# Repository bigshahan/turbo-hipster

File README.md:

turbo-hipster
=============

# Running the site for devlopment (Windows) (Works for Linux/OS X too)

Install git, VirtualBox, Vagrant. Then from git project folder:

	vagrant up
	vagrant ssh
	cd /vagrant
	jekyll serve -w

# Running the site for development (Linux and OS X)

Make sure ruby and nodejs is installed. Then from the git project folder, do:
	gem install rmagick
	gem install jekyll
	bundle install

then:

	jekyll serve -w

# Adding a New Project

# Setting Up the Production Server

# Helpful Commands

To check status in github powershell:

	git status -s

To update:

	git pull

To make changes:

	git status -s
	git add filename				// Variations for making changes
	git commit -m "comment here"	//
	git push

Shortcut for updating old files:

	Replace above variation // with
	git commit -a -m "comment here"

Shortcut for adding all files in a folder:

	Replace above variation // with
	git add foldername/*
	git commit -m "comment here"
	
	example:
	git add images/pipettebot/*
	git commit -m "Adds all files in local repository in images/pipettebot/ to main branch online"

# Enabling a Sidebar for a page

	Page Name
	=========

	<div class="col-sm-4">
		<ul class="nav nav-pills nav-stacked">
			{% sidebar "content1", "Content 1" %}

			{% sidebar "content2", "Content 2" %}

			{% sidebar "content3", "Content 3" %}
		</ul>
	</div>

	<div id="content1" class="sidebar-content col-sm-8">
		<h1>Content 1</h1>
		<p>text</p>
	</div>

	<div id="content2" class="sidebar-content col-sm-8">
		<h1>Content 2</h1>
		<p>text2</p>
	</div>

	<div id="content3" class="sidebar-content col-sm-8">
		<h1>Content 3</h1>
		<p>text3</p>
	</div>

# Pushing to the FTP server
(only works on Mac/Linux & must have lftp installed. The vagrant image has this installed) 

cd into the project folder
./upload.sh 

Username & FTP server is set in the deploy.x file

# Using Git GUI
Use the folder where the repository is held from github

	Click rescan button to check if any new changes have been made
	Click files you want to change in the unstaged changes section and press stage changed button
	Then after selecting all desired files press commit button
	Then press push button to make changes to the main repository

# References
- Boostrap: http://getbootstrap.com/
- Vagrant / Jekyll: https://coderwall.com/p/xrfadg
- Jekyll documentation: http://jekyllrb.com/
- Markdown Syntax: https://github.com/adam-p/markdown-here/wiki/Markdown-Cheatsheet

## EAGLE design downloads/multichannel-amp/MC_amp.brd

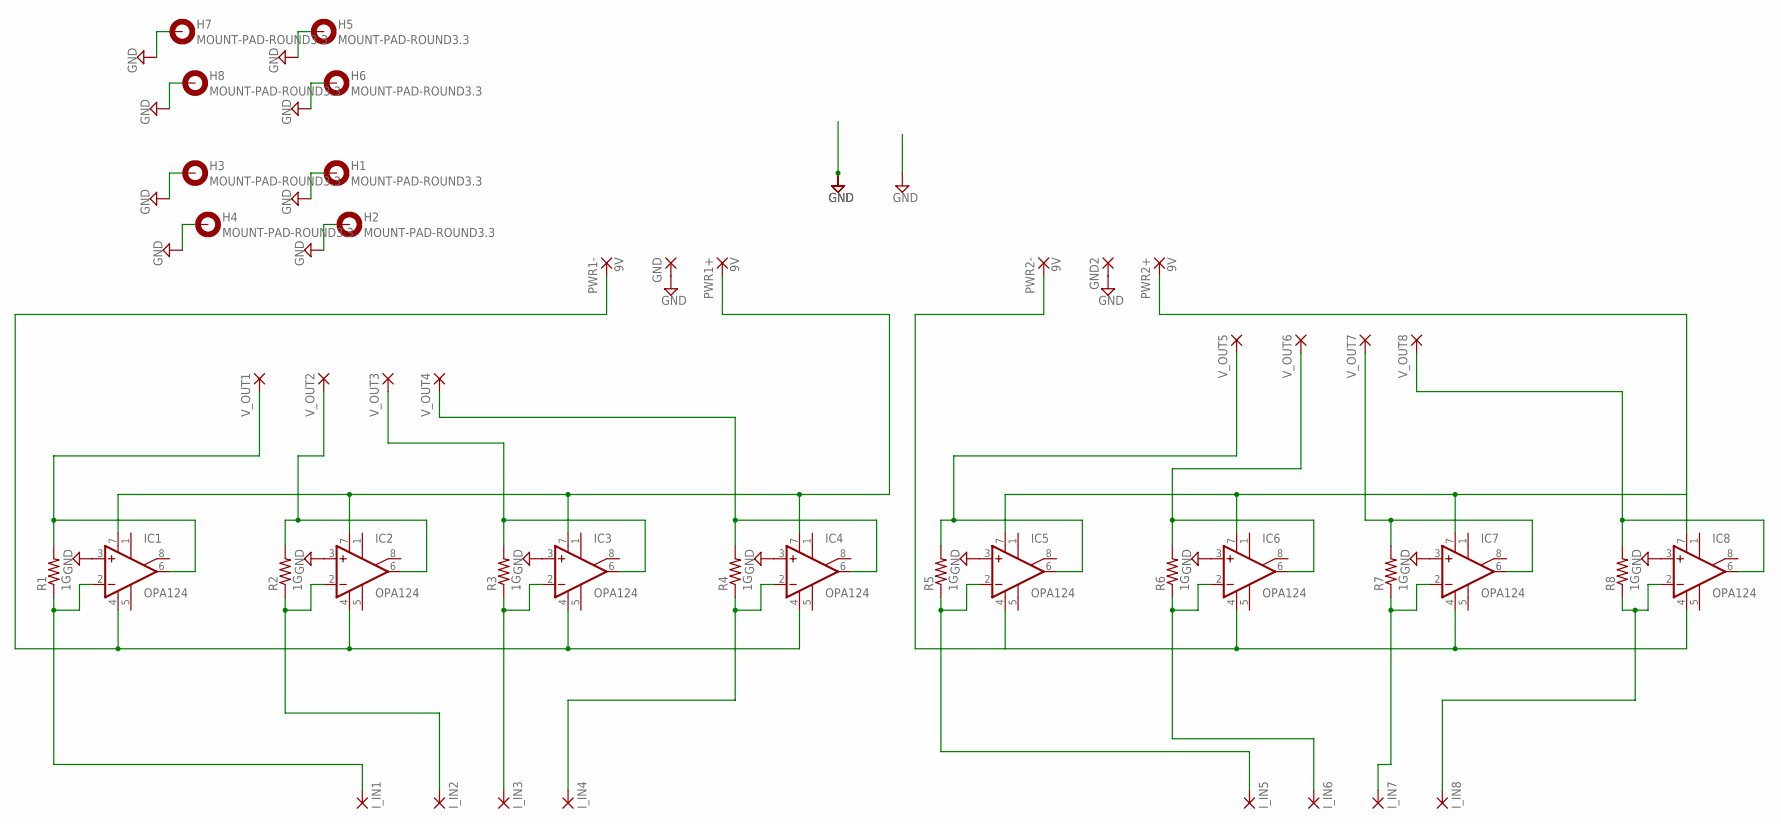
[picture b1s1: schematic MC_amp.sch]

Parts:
GND, GND2: 1,6/0,8
H1, H2, H3, H4, H5, H6, H7, H8: MOUNT-PAD-ROUND3.3; 3,3-PAD
IC1, IC2, IC3, IC4, IC5, IC6, IC7, IC8: OPA124; DIL08
I_IN1, I_IN2, I_IN3, I_IN4, I_IN5, I_IN6, I_IN7, I_IN8: 1,6/0,8
PWR1+, PWR1-, PWR2+, PWR2-: 9V; 1,6/0,8
R1, R2, R3, R4, R5, R6, R7, R8: 1G; 0309/12
V_OUT1, V_OUT2, V_OUT3, V_OUT4, V_OUT5, V_OUT6, V_OUT7, V_OUT8: 1,6/0,8

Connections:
GND: GND.1, GND2.1, H1.B3,3, H2.B3,3, H3.B3,3, H4.B3,3, H5.B3,3, H6.B3,3, H7.B3,3, H8.B3,3, IC1.3 (+IN), IC2.3 (+IN), IC3.3 (+IN), IC4.3 (+IN), IC5.3 (+IN), IC6.3 (+IN), IC7.3 (+IN), IC8.3 (+IN)
unnamed: IC1.2 (-IN), I_IN1.1, R1.1
unnamed: IC1.6 (OUT), R1.2, V_OUT1.1
unnamed: IC1.7 (V+), IC2.7 (V+), IC3.7 (V+), IC4.7 (V+), PWR1+.1
unnamed: IC2.6 (OUT), R2.2, V_OUT2.1
unnamed: IC2.2 (-IN), I_IN2.1, R2.1
unnamed: IC3.2 (-IN), I_IN3.1, R3.1
unnamed: IC3.6 (OUT), R3.2, V_OUT3.1
unnamed: IC5.4 (V-), IC6.4 (V-), IC7.4 (V-), IC8.4 (V-), PWR2-.1
unnamed: IC4.2 (-IN), I_IN4.1, R4.1
unnamed: IC4.6 (OUT), R4.2, V_OUT4.1
unnamed: IC5.2 (-IN), I_IN5.1, R5.1
unnamed: IC5.6 (OUT), R5.2, V_OUT5.1
unnamed: IC5.7 (V+), IC6.7 (V+), IC7.7 (V+), IC8.7 (V+), PWR2+.1
unnamed: IC6.2 (-IN), I_IN6.1, R6.1
unnamed: IC6.6 (OUT), R6.2, V_OUT6.1
unnamed: IC7.2 (-IN), I_IN7.1, R7.1
unnamed: IC7.6 (OUT), R7.2, V_OUT7.1
unnamed: IC8.2 (-IN), I_IN8.1, R8.1
unnamed: IC8.6 (OUT), R8.2, V_OUT8.1
unnamed: IC1.4 (V-), IC2.4 (V-), IC3.4 (V-), IC4.4 (V-), PWR1-.1

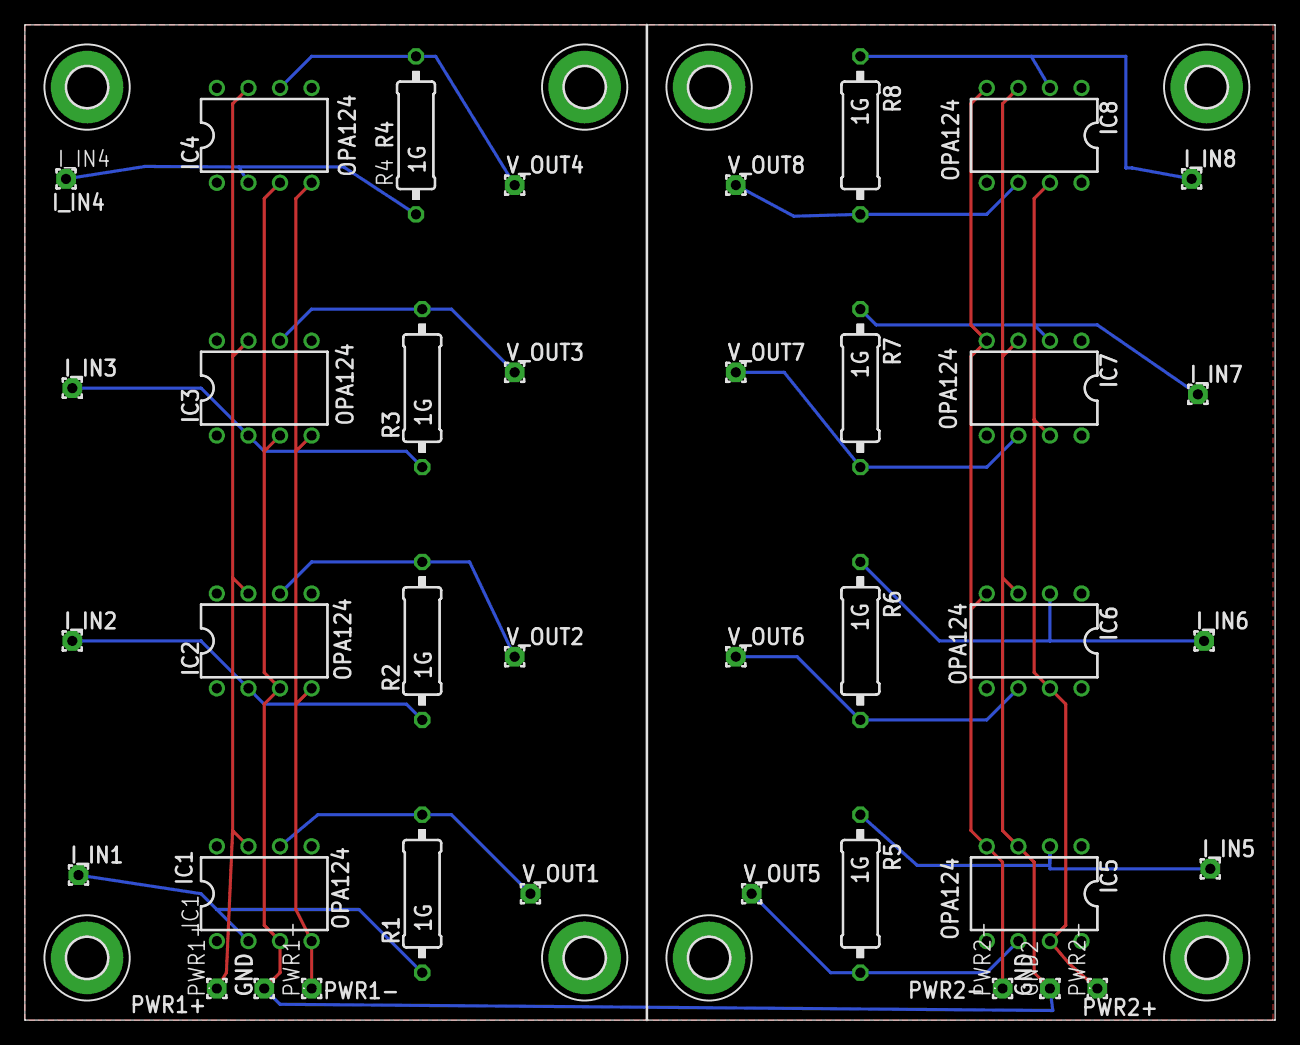
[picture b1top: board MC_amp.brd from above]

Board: 2 copper layers, 100.5 x 80.0 mm, 46 parts (0 on the bottom side), 21 nets.

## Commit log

2014-04-22 Initial rails project
2014-04-22 Updated copyright
2014-04-22 Removed default file that is not needed.
2014-04-22 Windows dependencies.
2014-05-18 Switching to jekyll
2014-05-18 Updated Readme for development
2014-05-18 Started work on projects folder and gemfile
2014-05-18 Added VagrantFile
2014-05-18 Folders for iamges
2014-05-18 Organized the projects
2014-05-18 Updated Vagrantfile for correct jekyll version
2014-05-18 Updated gitignore to ignore vagrant.
2014-05-19 Readme now has Markdown syntax info
2014-05-30 Placeholders in readme
2014-06-03 Started adding in tabs for projects.
2014-06-03 Adding in support for Bootstrap 3
2014-06-03 Fixed header.
2014-06-03 Fixed footer.
2014-06-03 More bootstrap fixes.
2014-06-03 Tabs kind of work.
2014-06-03 Basic page templates for PipetteBot
2014-06-03 Fixed page / post layotus
2014-06-03 Added Pipettebot basic content
2014-06-03 Added downloads folder
2014-06-03 Added files PipettebotCode.ino and support.SLDPRT
2014-06-03 Page header works now.
2014-06-03 Updated link for support cad download
2014-06-03 Project tabs work.
2014-06-03 Changed PIpetteBot CAD table to html
2014-06-03 Updated BOM to HTML
2014-06-03 Bug fix
2014-06-03 README formatting issues.
2014-06-04 Doubled CAD Table
2014-06-04 Deleted unneeded file
2014-06-04 Added Code table to CAD tab
2014-06-04 Added folders for drawbot and multichannel amp.
2014-06-04 Added basic files for drawbot and multichannel-amp
2014-06-05 added subdirs to MCA
2014-06-05 Updated description and BOM
2014-06-06 Began Drawbot info
2014-06-10 Sample instructions template.
2014-06-19 Updated pipbot instruc and bom
2014-06-19 Further updated pipbot instruc and bom
2014-06-25 Support for comments
2014-06-26 Updated motion component instructions with images
2014-06-26 Seperated Electronics from Coding in pipettebot
2014-06-26 Removed extra section step 4 and 5 in pipettebot instructions
2014-06-26 Added Sensors section in pipettebot
2014-06-26 Test Git GUI
2014-06-26 Updated Readme with helpful commands
2014-06-26 Added comments on using Git GUI
2014-07-03 Pipettebot instructions for automated wellplate
2014-07-07 Sidebar support and sample code in REadme
2014-07-09 updates instructions to sidebar format
2014-07-10 updated pipbot instruction
2014-07-10 updates pipbot instructions pictures
2014-07-10 Added an Outline for the Coding Section in pipettebot in instructions
2014-07-10 Started work on automatic thumbnail generation.
2014-07-10 Added custom thumbnail tag.
2014-07-10 Comments now span full width of page.
2014-07-10 Started converting PipetteBot instructions to new style
2014-07-10 Responsive bug fix to thumbnail
2014-07-10 Thumbnail: Cleaned up code a bit
2014-07-10 Thumbnail: Thumbnail generation not really working yet
2014-07-10 Thumbnail generation works. For some reason jekyll deletes them post generating them
2014-07-10 Thumbnail generation bug has been fixed!
2014-07-17 Added lftp to vagrant file
2014-07-17 Updated vagrant file
2014-07-17 More updates to instructions
    Including side tabs and finishing build
2014-07-17 Deleting unused files
2014-07-21 Further updates to pipettebot instructions
2014-07-31 Various updates to pipbot instructions including updated images for lasercut/3d printing sections
2014-08-07 Added downloads
2014-08-11 Finished Lasercut and 3D Printed Components on pipbot instructions
2014-08-11 Finished up well plate replacement section and etc in pipbot instructions
2014-08-11 Finished up sensors section in pipbot instructions
2014-08-12 Further updates to pipettebot instruction
2014-08-13 Further updates to pippetebot instructions
2014-08-14 Easy ftp uploading script
2014-08-20 Pipettebot instructions: edit tip removal, finish pipette mount, rough draft assembly.
2014-08-25 Image / Dreamhost bug fixe
2014-08-25 Changed X/Z axis in pipettebot instructions
2014-08-25 Swapped Y/Z axes. Finished up final assembly section in pipettebot instrucitons
2014-08-26 Rough draft of calibration in pipettebot instruction
2014-08-26 Finished electronics portion of pipettebot instructions
2014-08-26 Rough of Pipettebot BOM
2014-09-05 Updated simple descriptions and contact info
2014-09-09 Edited pipettebot instructions: calibration, and hacking electronic pipette. Uploaded rar of cad folder
2014-09-09 Removed drawbot from projects
    temporarily removed drawbot from _projects until content is there;
    replace later
2014-09-10 Completed Pipettebot BOM
2014-09-12 Edited pipettebot instruction calibration steps
2014-10-19 Various edits in pipettebot
